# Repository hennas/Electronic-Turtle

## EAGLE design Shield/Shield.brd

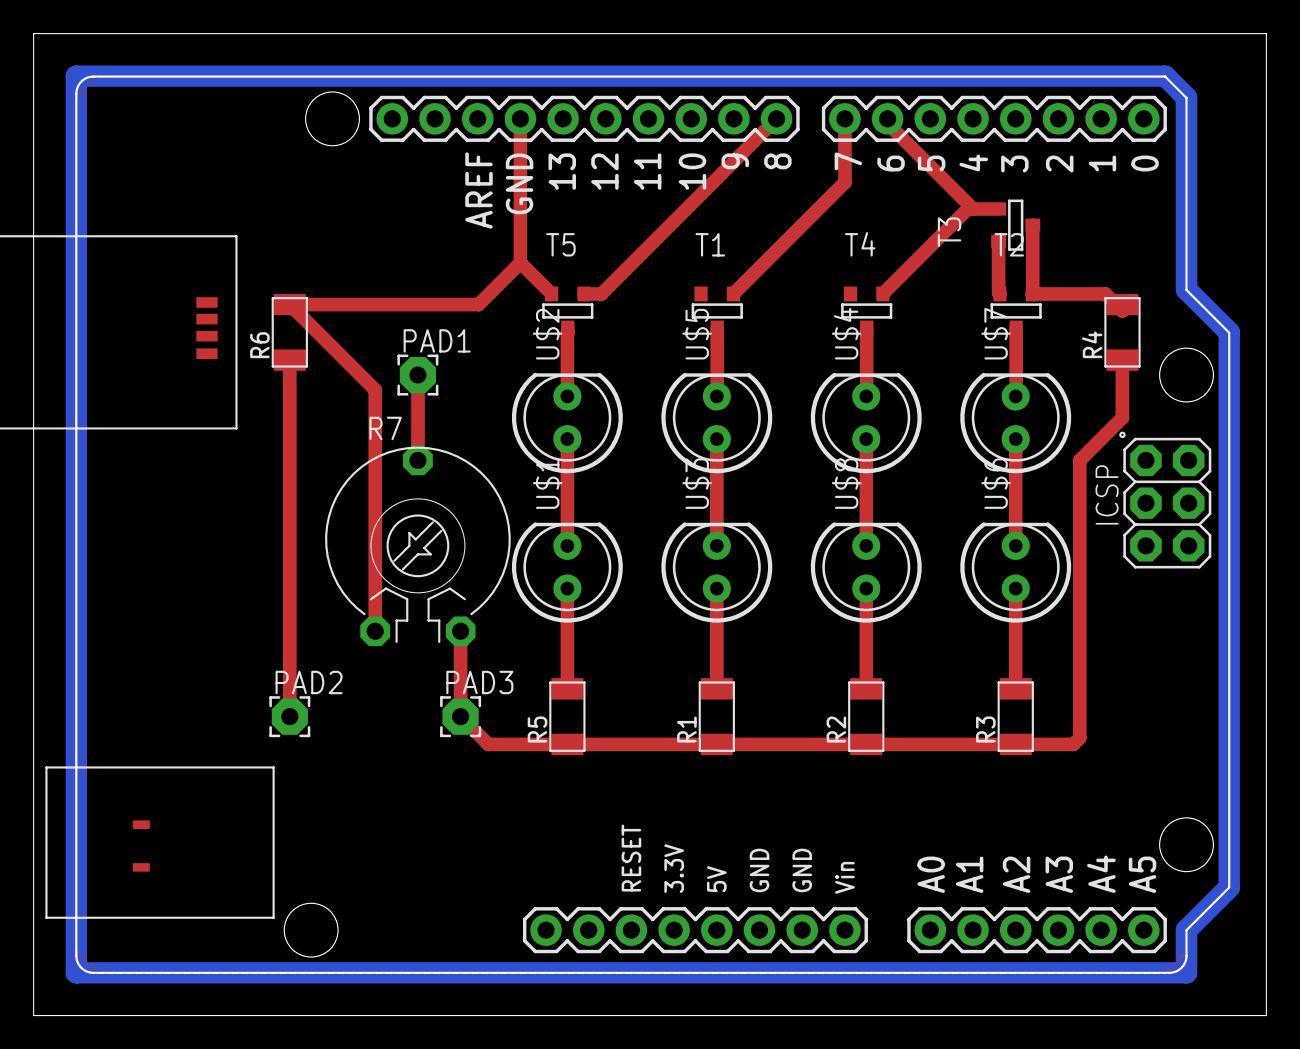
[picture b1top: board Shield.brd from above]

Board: 2 copper layers, 73.2 x 58.3 mm, 24 parts (0 on the bottom side), 20 nets.

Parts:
PAD1, PAD2, PAD3: 2,15/1,0
PCB1: ARDUINO_UNO
R1, R2, R3, R4, R5, R6: R1206FAB
R7: PT-10
T1, T2, T3, T4, T5: SOT-23
U$1, U$2, U$3, U$4, U$5, U$6, U$7, U$8: LED5MM; 5MM

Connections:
GND: PCB1.GND, PCB1.GND., PCB1.GND.., R6.2, R7.1, T1.2, T2.2, T3.2, T4.2, T5.2
unnamed: U$1.OUT, U$2.IN
unnamed: U$3.OUT, U$5.IN
unnamed: U$4.IN, U$8.OUT
unnamed: U$6.OUT, U$7.IN
unnamed: R5.2, U$1.IN
unnamed: R1.2, U$3.IN
unnamed: R2.2, U$8.IN
unnamed: R3.2, U$6.IN
unnamed: PAD1.1, R7.3
unnamed: T5.1, U$2.OUT
unnamed: T1.1, U$5.OUT
unnamed: T4.1, U$4.OUT
unnamed: PAD2.1, R6.1
unnamed: T2.1, U$7.OUT
unnamed: PCB1.8, T5.3
unnamed: PCB1.7, T1.3
unnamed: PCB1.6, T3.3, T4.3
unnamed: PAD3.1, R1.1, R2.1, R3.1, R4.1, R5.1, R7.2
unnamed: R4.2, T2.3, T3.1

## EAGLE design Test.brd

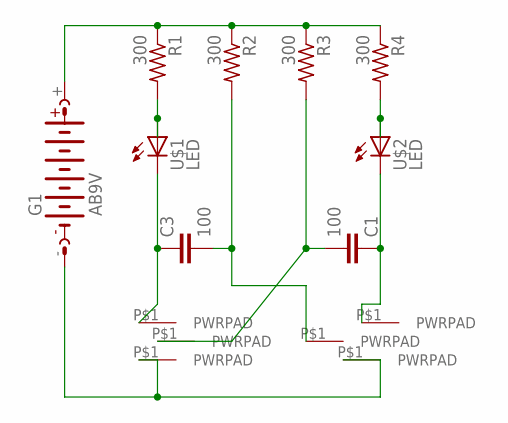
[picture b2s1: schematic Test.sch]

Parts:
C1, C3: 100; C1206
G1: AB9V
J1, J2, J3, J4, J5, J6: PWRPAD2-5MM; PWRPAD_2-5MM
R1, R2, R3, R4: 300; R1206
U$1, U$2: LED; LED1206

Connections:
unnamed: G1.+, R1.1, R2.1, R3.1, R4.1
unnamed: R1.2, U$1.1 (A)
unnamed: C3.1, J3.P$1, U$1.2 (C)
unnamed: C1.2, J2.P$1, R3.2
unnamed: C3.2, J4.P$1, R2.2
unnamed: R4.2, U$2.1 (A)
unnamed: C1.1, J5.P$1, U$2.2 (C)
unnamed: G1.-, J1.P$1, J6.P$1

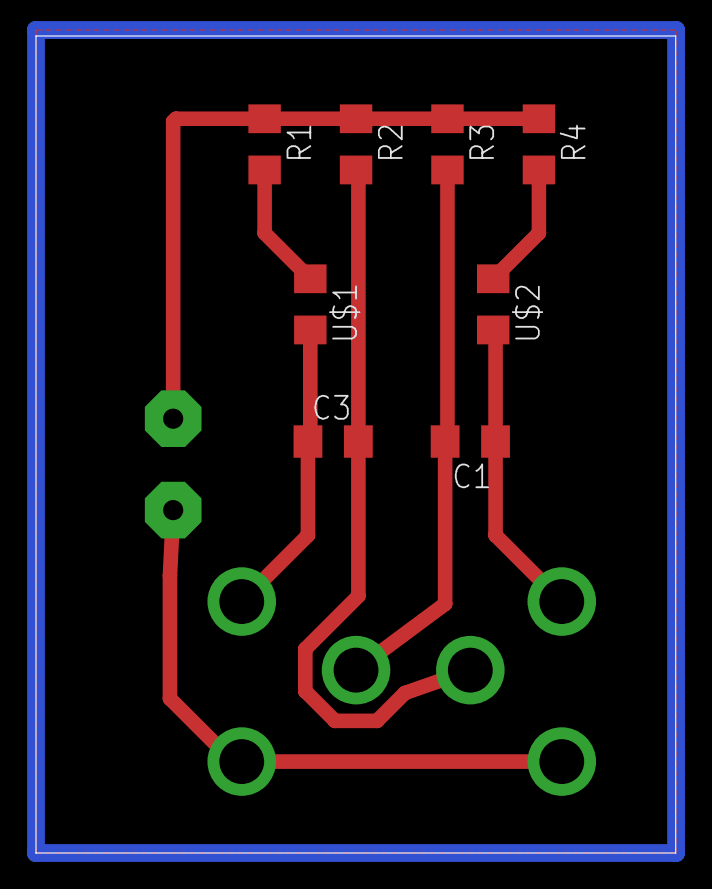
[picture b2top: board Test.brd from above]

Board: 2 copper layers, 35.5 x 45.4 mm, 15 parts (1 on the bottom side), 8 nets.
